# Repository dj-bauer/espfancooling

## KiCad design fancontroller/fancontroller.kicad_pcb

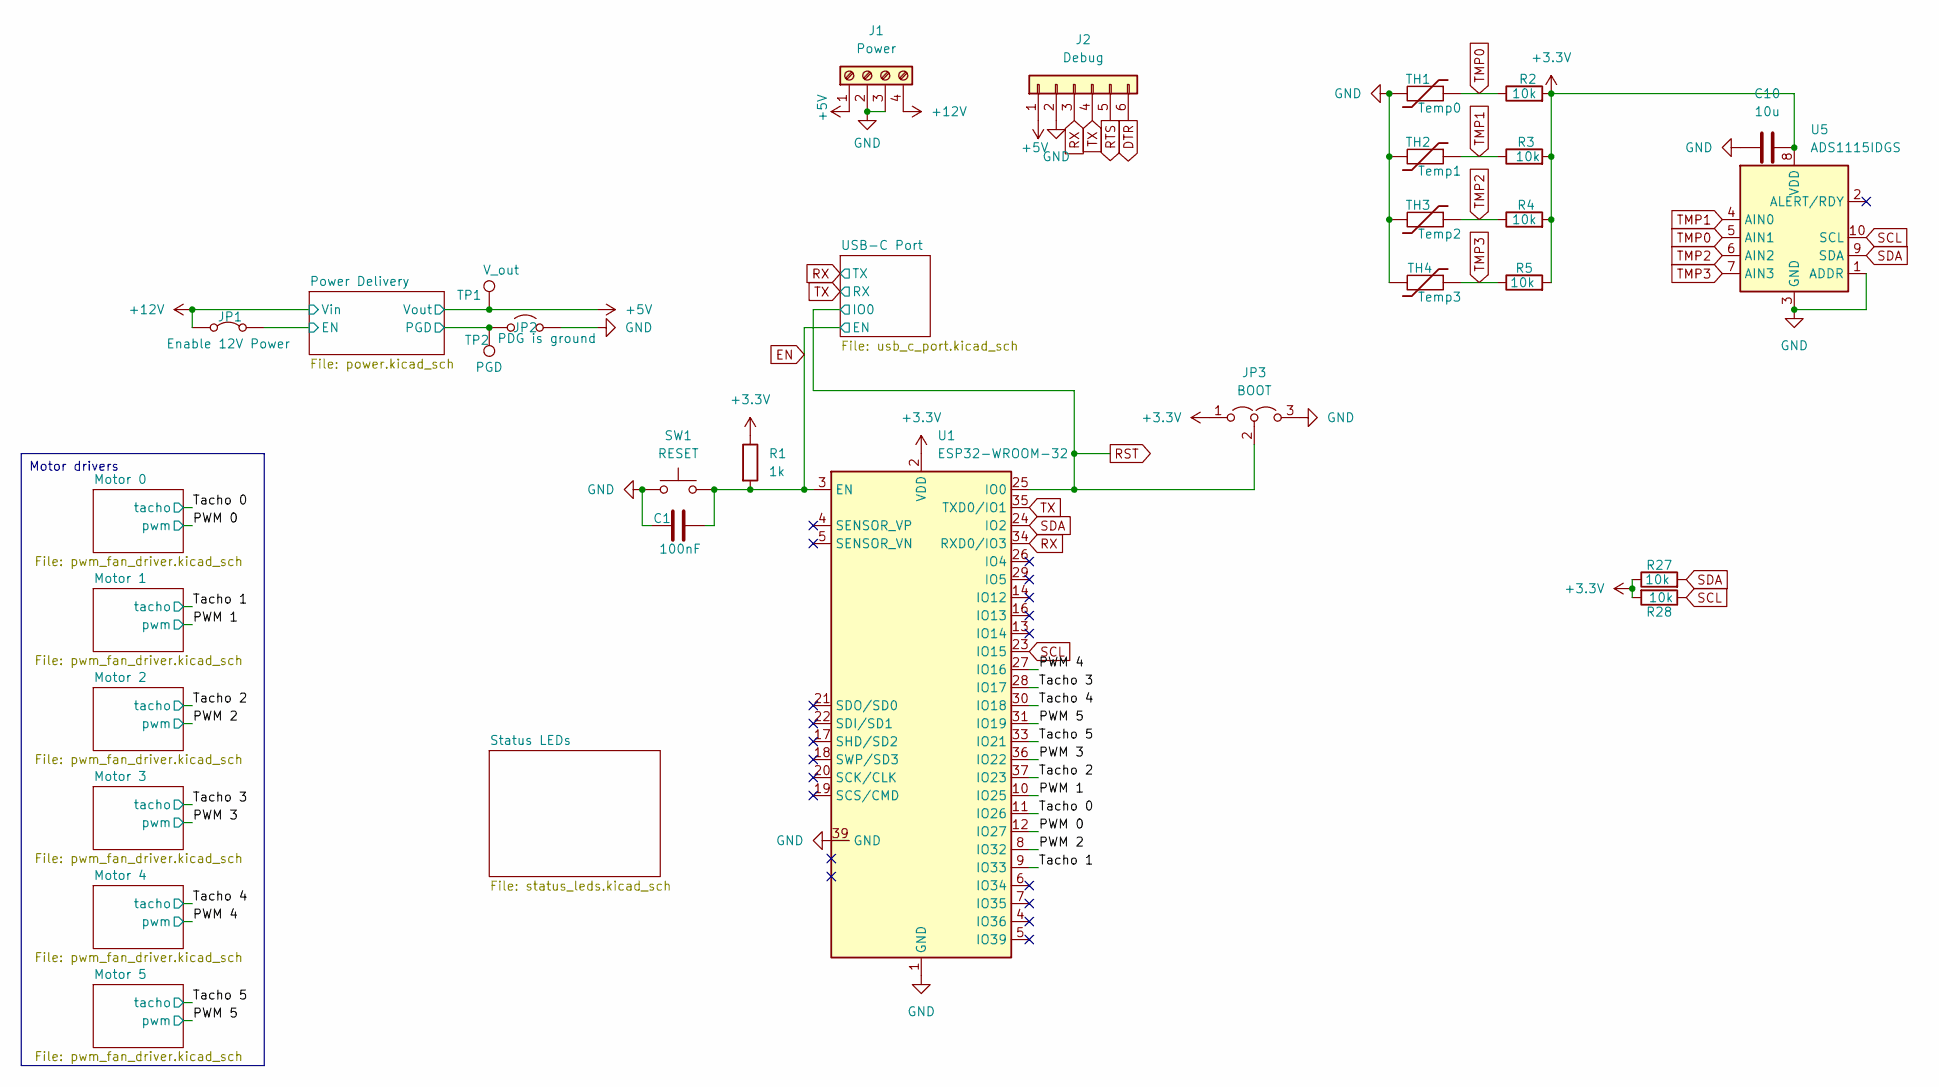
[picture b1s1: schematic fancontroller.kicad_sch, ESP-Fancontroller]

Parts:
C1: 100nF; C_0805_2012Metric; LCSC Part # C1525
C10: 10u
J1: Power; PinHeader_1x04_P2.54mm_Vertical; LCSC Part # C915913
J2: Debug; PinHeader_1x06_P2.54mm_Vertical; LCSC Part # C91552
JP1: Enable 12V Power; PinHeader_1x02_P2.54mm_Vertical; JLCPCB Rotation Offset 90
JP2: PDG is ground; PinHeader_1x02_P2.54mm_Vertical; JLCPCB Rotation Offset 90
JP3: BOOT; PinHeader_1x03_P2.54mm_Vertical; LCSC Part # C27985188
R1: 1k; R_0805_2012Metric; LCSC Part # C17513
R2, R3, R4, R5, R27, R28: 10k; R_0805_2012Metric; LCSC Part # C17414
SW1: RESET; PinHeader_1x02_P2.54mm_Vertical; LCSC Part # C5360898
TH1: Temp0; PinHeader_1x02_P2.54mm_Vertical; LCSC Part # C5360898
TH2: Temp1; PinHeader_1x02_P2.54mm_Vertical; LCSC Part # C5360898
TH3: Temp2; PinHeader_1x02_P2.54mm_Vertical; LCSC Part # C5360898
TH4: Temp3; PinHeader_1x02_P2.54mm_Vertical; LCSC Part # C5360898
TP1: V_out; TestPoint_Pad_2.5x2.5mm
TP2: PGD; TestPoint_Pad_2.5x2.5mm
U1: ESP32-WROOM-32; ESP32-WROOM-32E; LCSC Part # C2973652
U5: ADS1115IDGS; TSSOP-10_3x3mm_P0.5mm; LCSC Part # C37593

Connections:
+3.3V: C10.2, JP3.1 (A), R1.1, R2.2, R3.2, R4.2, R5.2, R27.1, R28.2, U1.2 (VDD), U5.8 (VDD); also elsewhere on the board
+5V: J1.1, J2.1, TP1.1; also elsewhere on the board
+12V: J1.4, JP1.1 (A); also elsewhere on the board
/PWM 0: U1.12 (IO27); also elsewhere on the board
/PWM 1: U1.10 (IO25); also elsewhere on the board
/PWM 2: U1.8 (IO32); also elsewhere on the board
/PWM 3: U1.36 (IO22); also elsewhere on the board
/PWM 4: U1.27 (IO16); also elsewhere on the board
/PWM 5: U1.31 (IO19); also elsewhere on the board
/Power Delivery/EN: JP1.2 (B); also elsewhere on the board
/Power Delivery/PGD: JP2.1 (A), TP2.1; also elsewhere on the board
/Tacho 0: U1.11 (IO26); also elsewhere on the board
/Tacho 1: U1.9 (IO33); also elsewhere on the board
/Tacho 2: U1.37 (IO23); also elsewhere on the board
/Tacho 3: U1.28 (IO17); also elsewhere on the board
/Tacho 4: U1.30 (IO18); also elsewhere on the board
/Tacho 5: U1.33 (IO21); also elsewhere on the board
DTR: J2.6; also elsewhere on the board
EN: C1.1, R1.2, SW1.2, U1.3 (EN); also elsewhere on the board
GND: C1.2, C10.1, J1.2, J1.3, J2.2, JP2.2 (B), JP3.3 (B), SW1.1, TH1.2, TH2.2, TH3.2, TH4.2, U1.1 (GND), U1.39 (GND), U5.1 (ADDR), U5.3 (GND); also elsewhere on the board
RST: JP3.2 (C), U1.25 (IO0); also elsewhere on the board
RTS: J2.5; also elsewhere on the board
RX: J2.3, U1.34 (RXD0/IO3); also elsewhere on the board
SCL: R28.1, U1.23 (IO15), U5.10 (SCL)
SDA: R27.2, U1.24 (IO2), U5.9 (SDA)
TMP0: R2.1, TH1.1, U5.5 (AIN1)
TMP1: R3.1, TH2.1, U5.4 (AIN0)
TMP2: R4.1, TH3.1, U5.6 (AIN2)
TMP3: R5.1, TH4.1, U5.7 (AIN3)
TX: J2.4, U1.35 (TXD0/IO1); also elsewhere on the board

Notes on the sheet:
Motor drivers

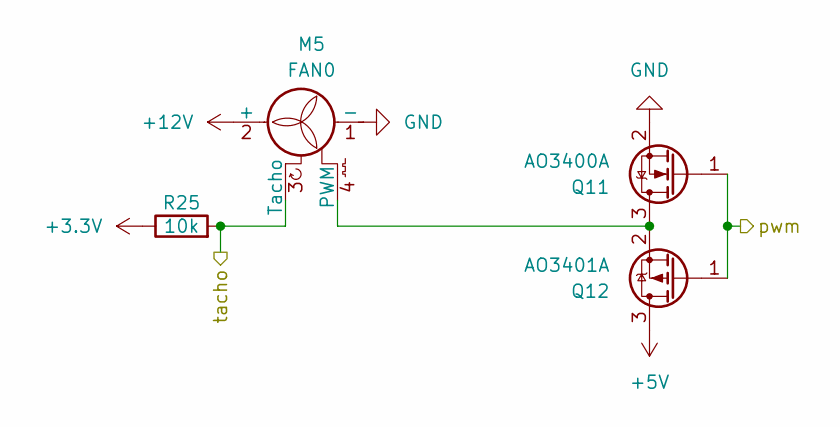
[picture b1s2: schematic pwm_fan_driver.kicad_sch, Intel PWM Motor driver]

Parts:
M5: FAN0; FanPinHeader_1x04_P2.54mm_Vertical; LCSC Part # C402778
Q11: AO3400A; SOT-23; LCSC Part # C20917
Q12: AO3401A; SOT-23; LCSC Part # C15127
R25: 10k; R_0805_2012Metric; LCSC Part # C17414

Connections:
+3.3V: R25.1; also elsewhere on the board
+5V: Q12.3 (D); also elsewhere on the board
+12V: M5.2 (+); also elsewhere on the board
/PWM 4: Q11.1 (G), Q12.1 (G); also elsewhere on the board
/Tacho 4: M5.3 (Tacho), R25.2; also elsewhere on the board
GND: M5.1 (-), Q11.2 (S); also elsewhere on the board
unnamed: M5.4 (PWM), Q11.3 (D), Q12.2 (S)

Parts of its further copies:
M1, M2, M3, M4, M6: FAN0; FanPinHeader_1x04_P2.54mm_Vertical; LCSC Part # C402778
Q3, Q5, Q7, Q9, Q13: AO3400A; SOT-23; LCSC Part # C20917
Q4, Q6, Q8, Q10, Q14: AO3401A; SOT-23; LCSC Part # C15127
R21, R22, R23, R24, R26: 10k; R_0805_2012Metric; LCSC Part # C17414

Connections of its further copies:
+3.3V: R21.1, R22.1, R23.1, R24.1, R26.1; also elsewhere on the board
+5V: Q4.3 (D), Q6.3 (D), Q8.3 (D), Q10.3 (D), Q14.3 (D); also elsewhere on the board
+12V: M1.2 (+), M2.2 (+), M3.2 (+), M4.2 (+), M6.2 (+); also elsewhere on the board
/PWM 0: Q5.1 (G), Q6.1 (G); also elsewhere on the board
/PWM 1: Q3.1 (G), Q4.1 (G); also elsewhere on the board
/PWM 2: Q7.1 (G), Q8.1 (G); also elsewhere on the board
/PWM 3: Q9.1 (G), Q10.1 (G); also elsewhere on the board
/PWM 5: Q13.1 (G), Q14.1 (G); also elsewhere on the board
/Tacho 0: M2.3 (Tacho), R22.2; also elsewhere on the board
/Tacho 1: M1.3 (Tacho), R21.2; also elsewhere on the board
/Tacho 2: M3.3 (Tacho), R23.2; also elsewhere on the board
/Tacho 3: M4.3 (Tacho), R24.2; also elsewhere on the board
/Tacho 5: M6.3 (Tacho), R26.2; also elsewhere on the board
GND: M1.1 (-), M2.1 (-), M3.1 (-), M4.1 (-), M6.1 (-), Q3.2 (S), Q5.2 (S), Q7.2 (S), Q9.2 (S), Q13.2 (S); also elsewhere on the board
unnamed: M1.4 (PWM), Q3.3 (D), Q4.2 (S)
unnamed: M2.4 (PWM), Q5.3 (D), Q6.2 (S)
unnamed: M3.4 (PWM), Q7.3 (D), Q8.2 (S)
unnamed: M4.4 (PWM), Q9.3 (D), Q10.2 (S)
unnamed: M6.4 (PWM), Q13.3 (D), Q14.2 (S)

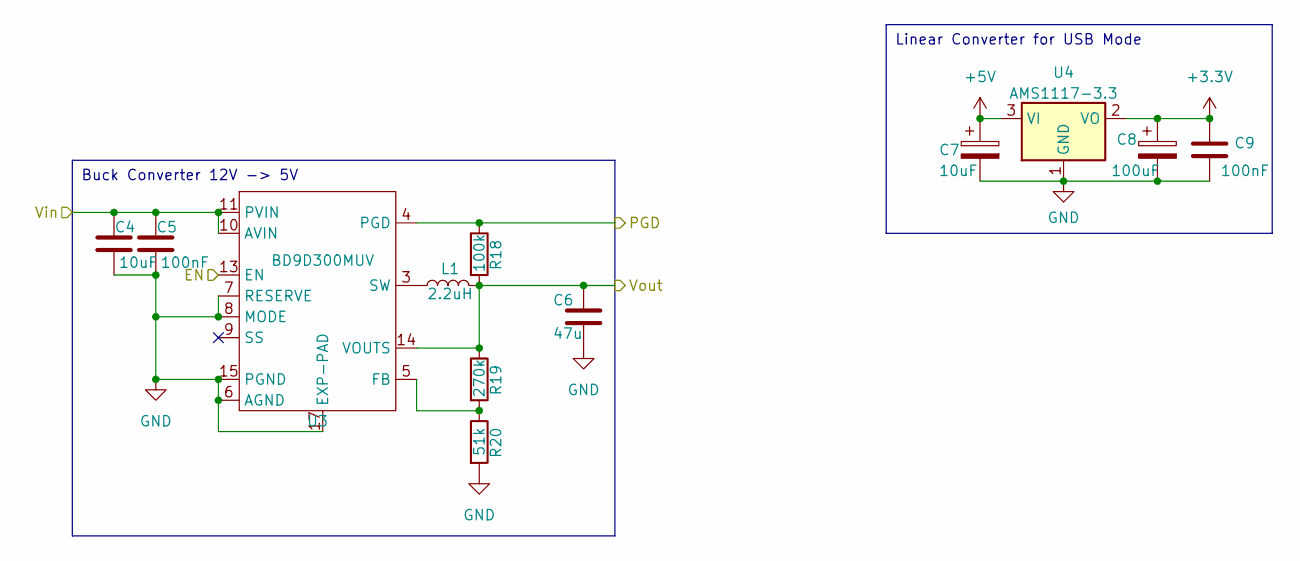
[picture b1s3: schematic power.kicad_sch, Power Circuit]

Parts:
C4, C7: 10uF; C_0805_2012Metric; LCSC Part # C440198
C5, C9: 100nF; C_0805_2012Metric; LCSC Part # C1525
C6: 47u; C_0805_2012Metric; LCSC Part # C16780
C8: 100uF; CP_Elec_10x10; LCSC Part # C249836
L1: 2.2uH; L_0805_2012Metric; LCSC Part # C479919
R18: 100k; R_0805_2012Metric; LCSC Part # C149504
R19: 270k; R_0805_2012Metric; LCSC Part # C17589
R20: 51k; R_0805_2012Metric; LCSC Part # C17737
U3: BD9D300MUV; VQFN-16-1EP_3x3mm_P0.5mm_EP1.45x1.45mm; LCSC Part # C2071880
U4: AMS1117-3.3; SOT-223; LCSC Part # C6186

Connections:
+3.3V: C8.1, C9.1, U4.2 (VO); also elsewhere on the board
+5V: C6.1, C7.1, L1.2, R18.2, R19.1, U3.14 (VOUTS), U4.3 (VI); also elsewhere on the board
+12V: C4.1, C5.1, U3.10 (AVIN), U3.11 (PVIN), U3.12 (PVIN); also elsewhere on the board
/Power Delivery/EN: U3.13 (EN); also elsewhere on the board
/Power Delivery/PGD: R18.1, U3.4 (PGD); also elsewhere on the board
GND: C4.2, C5.2, C6.2, C7.2, C8.2, C9.2, R20.2, U3.6 (AGND), U3.7 (RESERVE), U3.8 (MODE), U3.15 (PGND), U3.16 (PGND), U3.17 (EXP-PAD), U4.1 (GND); also elsewhere on the board
unnamed: L1.1, U3.1 (SW), U3.2 (SW), U3.3 (SW)
unnamed: R19.2, R20.1, U3.5 (FB)

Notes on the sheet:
Buck Converter 12V -> 5V
Linear Converter for USB Mode

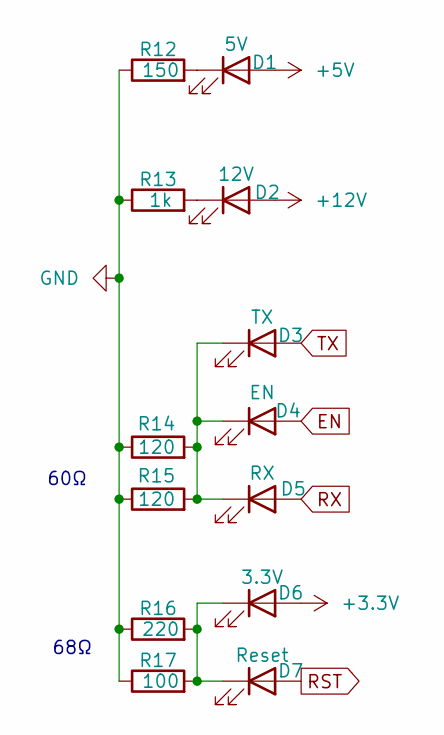
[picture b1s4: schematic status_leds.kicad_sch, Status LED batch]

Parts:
D1: 5V; LED_0805_2012Metric; LCSC Part # C84262
D2: 12V; LED_0805_2012Metric; LCSC Part # C84256
D3: TX; LED_0805_2012Metric; LCSC Part # C84257
D4: EN; LED_0805_2012Metric; LCSC Part # C84257
D5: RX; LED_0805_2012Metric; LCSC Part # C84257
D6: 3.3V; LED_0805_2012Metric; LCSC Part # C84262
D7: Reset; LED_0805_2012Metric; LCSC Part # C84262
R12: 150; R_0805_2012Metric; LCSC Part # C17471
R13: 1k; R_0805_2012Metric; LCSC Part # C17513
R14, R15: 120; R_0805_2012Metric; LCSC Part # C17437
R16: 220; R_0603_1608Metric; LCSC Part # C17557
R17: 100; R_0603_1608Metric; LCSC Part # C17408

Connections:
+3.3V: D6.2 (A); also elsewhere on the board
+5V: D1.2 (A); also elsewhere on the board
+12V: D2.2 (A); also elsewhere on the board
EN: D4.2 (A); also elsewhere on the board
GND: R12.1, R13.1, R14.1, R15.1, R16.1, R17.1; also elsewhere on the board
unnamed: D1.1 (K), R12.2
unnamed: D2.1 (K), R13.2
unnamed: D3.1 (K), D4.1 (K), D5.1 (K), R14.2, R15.2
unnamed: D6.1 (K), D7.1 (K), R16.2, R17.2
RST: D7.2 (A); also elsewhere on the board
RX: D5.2 (A); also elsewhere on the board
TX: D3.2 (A); also elsewhere on the board

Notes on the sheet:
68Ω
60Ω

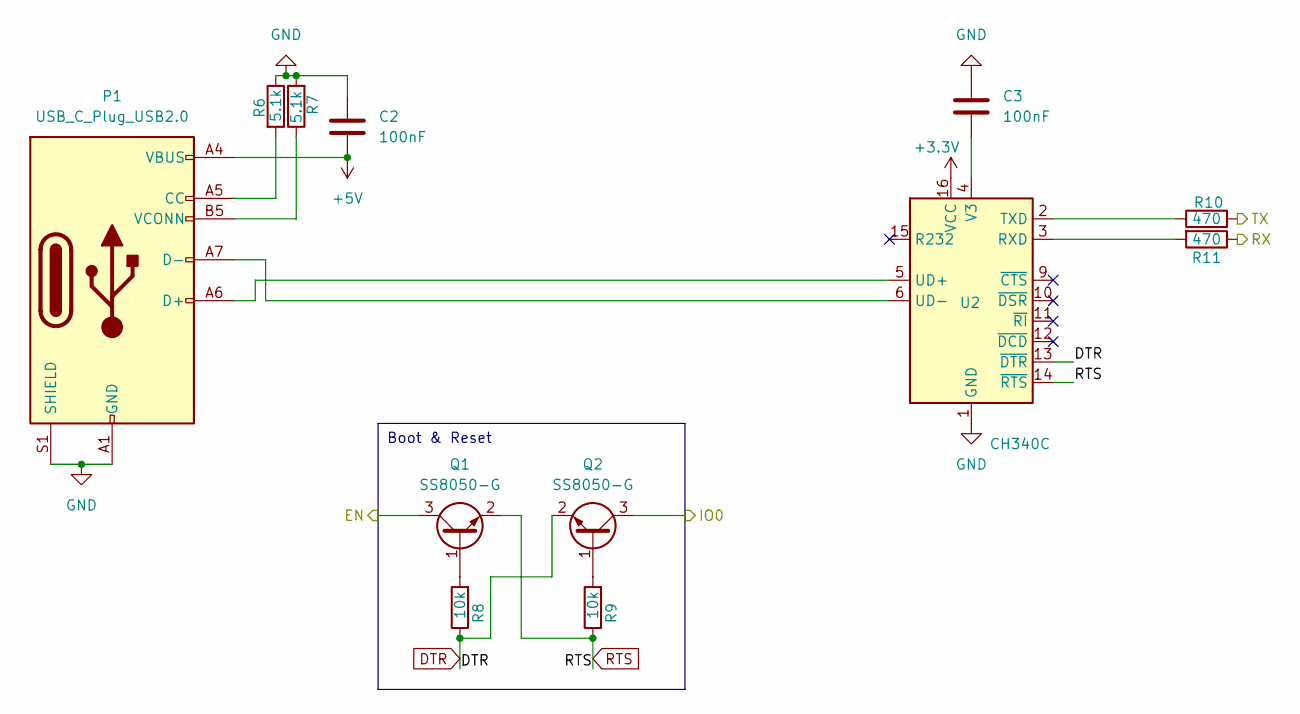
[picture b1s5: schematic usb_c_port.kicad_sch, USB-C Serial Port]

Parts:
C2, C3: 100nF; C_0805_2012Metric; LCSC Part # C1525
P1: USB_C_Plug_USB2.0; USB_C_Receptacle_HCTL_HC-TYPE-C-16P-01A; LCSC Part # C2894897
Q1, Q2: SS8050-G; SOT-23; LCSC Part # C2150
R6, R7: 5.1k; R_0805_2012Metric; LCSC Part # C27834
R8, R9: 10k; R_0805_2012Metric; LCSC Part # C17414
R10, R11: 470; R_0805_2012Metric; LCSC Part # C17710
U2: CH340C; SOIC-16_3.9x9.9mm_P1.27mm; LCSC Part # C84681

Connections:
+3.3V: U2.16 (VCC); also elsewhere on the board
+5V: C2.2, P1.A4 (VBUS), P1.A9 (VBUS), P1.B4 (VBUS), P1.B9 (VBUS); also elsewhere on the board
DTR: Q2.2 (E), R8.1, U2.13 (~DTR); also elsewhere on the board
EN: Q1.3 (C); also elsewhere on the board
GND: C2.1, C3.1, P1.A1 (GND), P1.A12 (GND), P1.B1 (GND), P1.B12 (GND), P1.S1 (SHIELD), R6.1, R7.2, U2.1 (GND); also elsewhere on the board
unnamed: P1.A5 (CC), R6.2
unnamed: P1.A6 (D+), U2.5 (UD+)
unnamed: P1.A7 (D-), U2.6 (UD-)
unnamed: P1.B5 (VCONN), R7.1
unnamed: Q1.1 (B), R8.2
unnamed: Q2.1 (B), R9.2
unnamed: R11.2, U2.3 (RXD)
unnamed: R10.1, U2.2 (TXD)
unnamed: C3.2, U2.4 (V3)
RST: Q2.3 (C); also elsewhere on the board
RTS: Q1.2 (E), R9.1, U2.14 (~RTS); also elsewhere on the board
RX: R10.2; also elsewhere on the board
TX: R11.1; also elsewhere on the board

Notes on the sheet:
Boot & Reset

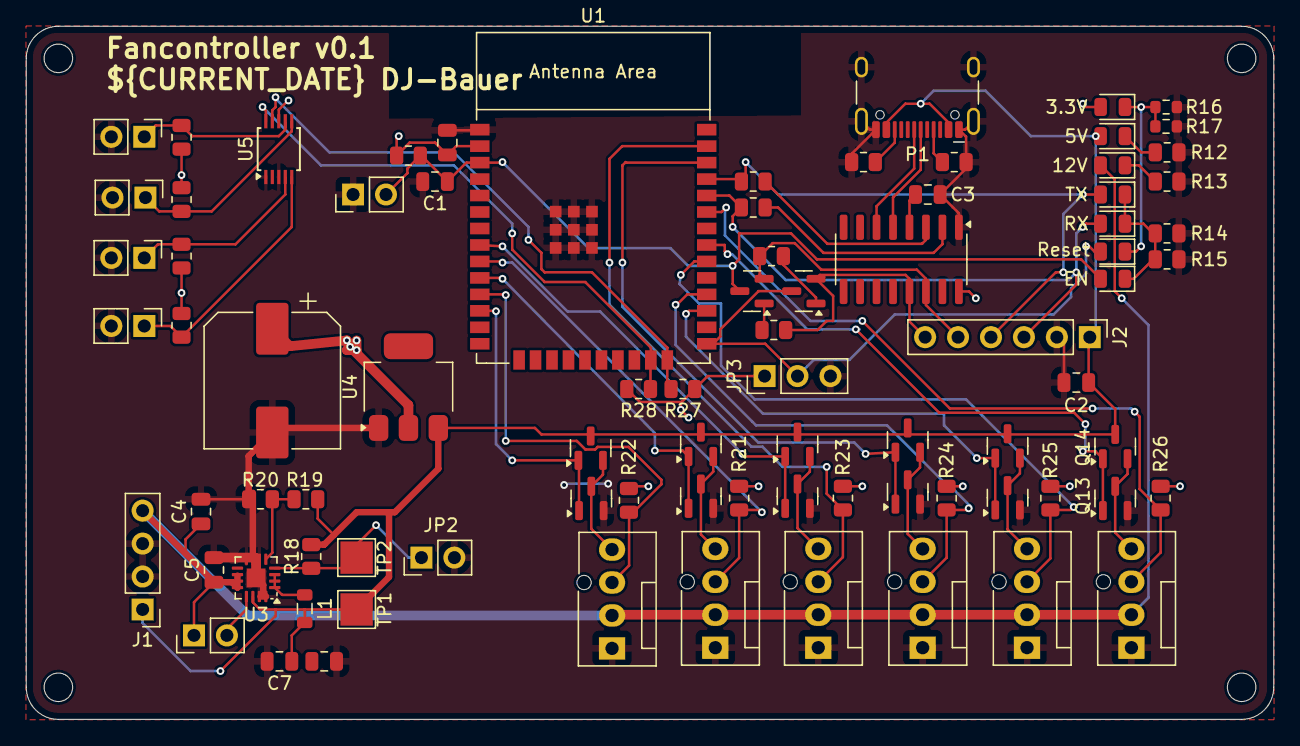
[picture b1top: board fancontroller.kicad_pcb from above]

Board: 2 copper layers, 96.2 x 53.4 mm, 88 parts (1 on the bottom side), 51 nets.

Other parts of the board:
GNU: Symbol_GNU-Logo_SilkscreenTop
H1, H2, H3, H4: MountingHole_2.2mm_M2

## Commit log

2024-04-17 Kicad Projekt angelegt
2024-04-26 KIcad messing
2024-05-15 Auf esp32 festlegen und schematik anfangen
2024-05-22 Massiver Fortschritt. Die Schematik scheint fertig zu sein und das tracing hat begonnen. Schritt für schritt werden Label von io vertauscht, um das tracen zu vereinfachen
2024-05-24 First pcb iteration done
2024-05-25 Update pcb
2024-05-29 FInish routing
2024-09-28 CMOS treiber für PWM output hinzugefügt, sicher ist sicher und extern pullup widerstände für Tacho inputs. Die sollten alle Teile für den ersten Prototypen sein.
    PCB Layout muss angepasst werden und neu geroutet werden. Danach ready für ersten prototypen :)
2024-09-30 Routing für ersten prototypen fertig und erste Teilnummern Parts zugeordnet für assembly preview
2024-10-02 JLCPCB order rotations fixed for most parts
2024-10-06 Move motor connection out in hirarchical sheet
2024-10-07 prepare to start dev on v1.2
2024-10-07 Break up into schematics and add USB-C programming interface
2024-10-07 Remove unused RF_Module custom library
2024-10-07 Restructure Fan drivers into separate modules and rework USB-C
2024-10-07 Improve footprints and do massive overhaul for part numbering for better future order
2024-10-07 Pretty rounded edgecut around pcb and start laying out LEDs
2024-10-08 Begin placing parts for v0.1 layout
2024-10-20 First firmware id
2024-10-20 edit schematic
2024-10-20 Stash pop
2024-11-04 Add i2c ADC
